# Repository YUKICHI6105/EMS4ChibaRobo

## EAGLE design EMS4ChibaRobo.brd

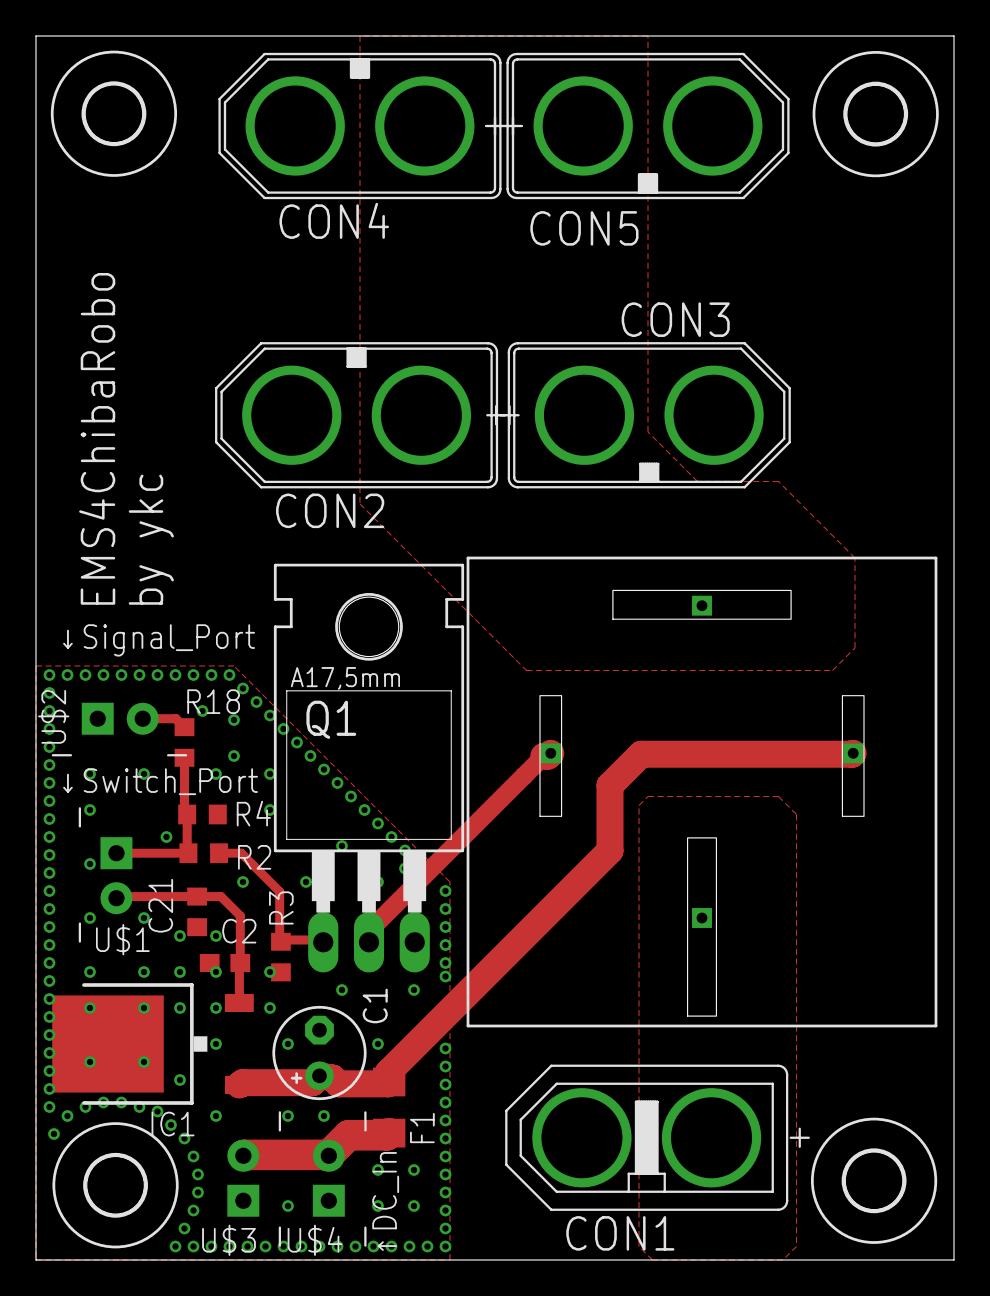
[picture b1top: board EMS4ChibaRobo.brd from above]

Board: 2 copper layers, 51.0 x 68.0 mm, 24 parts (0 on the bottom side), 11 nets.

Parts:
C1: 22u; E2,5-5
C2, C21: 100n; C0603
CON1: XT60PB-F
CON2, CON3, CON4, CON5: XT60PB-M
F1: R1206
H1, H2, H3, H4: MOUNT-HOLE3.2; 3,2
IC1: 7805DT; TO252
Q1: BUZ11BH; TO220BH
R2: 100R; R0603
R3, R4: 100k; R0603
R18: 1k; R0603
S1: 897-1AH-C-001
U$1, U$2, U$3, U$4: XH-2-STRAIGHT; CON-XH-2-STRAIGHT

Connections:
!EMS: R2.1, R4.1, R18.2, U$1.P$1
!EMS1: R18.1, U$2.P$2
+5V: C2.1, C21.2, IC1.2, U$1.P$2
+12V: C1.+, F1.2, IC1.1, S1.P$2
BATT_POWER: CON1.+, S1.P$1
GND2: CON1.-, CON2.-, CON3.-, CON4.-, CON5.-
GNDIO: C1.-, C2.2, C21.1, IC1.3, Q1.S, R3.2, R4.2, U$2.P$1, U$3.P$1, U$4.P$1
LOG_OUT: F1.1, U$3.P$2, U$4.P$2
unnamed: Q1.D, S1.P$3
unnamed: Q1.G, R2.2, R3.1
OUT_POWER_A: CON2.+, CON3.+, CON4.+, CON5.+, S1.P$4

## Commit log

2023-06-17 ねじ穴を修正
2023-06-28 大幅な設計変更
2023-08-09 relayのフットプリントの改善
2023-08-11 ランドの修正
2023-08-13 5V駆動に変更
2023-08-25 Update Relay
2023-09-11 シルクの調整
